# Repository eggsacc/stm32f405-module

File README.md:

<div align="center">

# STM32F405 Dev Module + BLDC hat

### MCU Dev
STM32F405RGT6 MCU dev module with commonly used peripherals broken out for easy access, and a dedicated CAN transceiver. Also includes 2 user programmable buttons and mini OLED display.

### BLDC Dev
BLDC hat based on the DRV8316C integrated driver. 6-PWM mode, 5-35V input, 5A continuous and 3-phase low-side current sensing. Suitable for FOC algorithm developement and testing for low current gimbal motors.

</div>

---

## MCU Pinout

<div align="center">

</div>

---

| Breakout / feature | Peripheral | Pin mapping |
|---|---|---|
| **UART header** | `USART3` | TX &rarr; `PC10`<br>RX &rarr; `PC11` |
| **SPI header** | `SPI1` | CS &rarr; `PA4`<br>SCK &rarr; `PA5`<br>MISO &rarr; `PA6`<br>MOSI &rarr; `PA7` |
| **I2C header** | `I2C1` | SCL &rarr; `PB6`<br>SDA &rarr; `PB7` |
| **CAN screw terminal** | `CAN1` (SN65HVD230) | TX &rarr; `PB9`<br>RX &rarr; `PB8` |
| **USB-C** | `USB_OTG_FS` | D&minus; &rarr; `PA11`<br>D+ &rarr; `PA12` |
| **SWD header** | `SYS` | SWDIO &rarr; `PA13`<br>SWCLK &rarr; `PA14` |
| **3-phase PWM header** | `TIM1` | <table><tbody><tr><td align="right">CH1 &rarr;</td><td><code>PA8</code></td><td align="right">&emsp;C1N &rarr;</td><td><code>PB13</code></td></tr><tr><td align="right">CH2 &rarr;</td><td><code>PA9</code></td><td align="right">&emsp;C2N &rarr;</td><td><code>PB0</code></td></tr><tr><td align="right">CH3 &rarr;</td><td><code>PA10</code></td><td align="right">&emsp;C3N &rarr;</td><td><code>PB1</code></td></tr></tbody></table> |
| **OLED** (on-board) | `I2C2` | SCL &rarr; `PB10`<br>SDA &rarr; `PB11` |
| **Utility buttons** (on-board) | `GPIO` / `EXTI` | L button &rarr; `PA2`<br>R button &rarr; `PA3` |
| **Crystal** (25MHz) | `RCC` HSE | OSC_IN &rarr; `PH0`<br>OSC_OUT &rarr; `PH1` |
| **GPIO header** (2&times;10) | free GPIO | <table><tbody><tr><td align="right">1 &rarr;</td><td><code>3.3V</code></td><td align="right">&emsp;2 &rarr;</td><td><code>3.3V</code></td></tr><tr><td align="right">3 &rarr;</td><td><code>5V</code></td><td align="right">&emsp;4 &rarr;</td><td><code>5V</code></td></tr><tr><td align="right">5 &rarr;</td><td><code>GND</code></td><td align="right">&emsp;6 &rarr;</td><td><code>GND</code></td></tr><tr><td align="right">7 &rarr;</td><td><code>PB4</code></td><td align="right">&emsp;8 &rarr;</td><td><code>PB3</code></td></tr><tr><td align="right">9 &rarr;</td><td><code>PC12</code></td><td align="right">&emsp;10 &rarr;</td><td><code>PC2</code></td></tr><tr><td align="right">11 &rarr;</td><td><code>PC3</code></td><td align="right">&emsp;12 &rarr;</td><td><code>PA0</code></td></tr><tr><td align="right">13 &rarr;</td><td><code>PA1</code></td><td align="right">&emsp;14 &rarr;</td><td><code>PC9</code></td></tr><tr><td align="right">15 &rarr;</td><td><code>PC8</code></td><td align="right">&emsp;16 &rarr;</td><td><code>PC7</code></td></tr><tr><td align="right">17 &rarr;</td><td><code>PC6</code></td><td align="right">&emsp;18 &rarr;</td><td><code>PB15</code></td></tr><tr><td align="right">19 &rarr;</td><td><code>PB14</code></td><td align="right">&emsp;20 &rarr;</td><td><code>PB12</code></td></tr></tbody></table> |

> Buttons are active-low to GND (3V3 pull-up).

---

## Power

>[!warning]Shared +5V rail
>5V rails are shared; do not connect USB and external power simultaneously!

- **USB-C**, 2-pin **`5V IN`** header, or `5V` on 2x10 breakout.
- AP2112K-3.3 LDO provides the 3.3 V rail (600 mA max).

---

## BLDC Hat hardware
<div align="center">

</div>

---
<div align="center">
Designed by <b>@eggsacc</b> · F405 Dev. V1.1<br>
Updated 22/09/2026
</div>

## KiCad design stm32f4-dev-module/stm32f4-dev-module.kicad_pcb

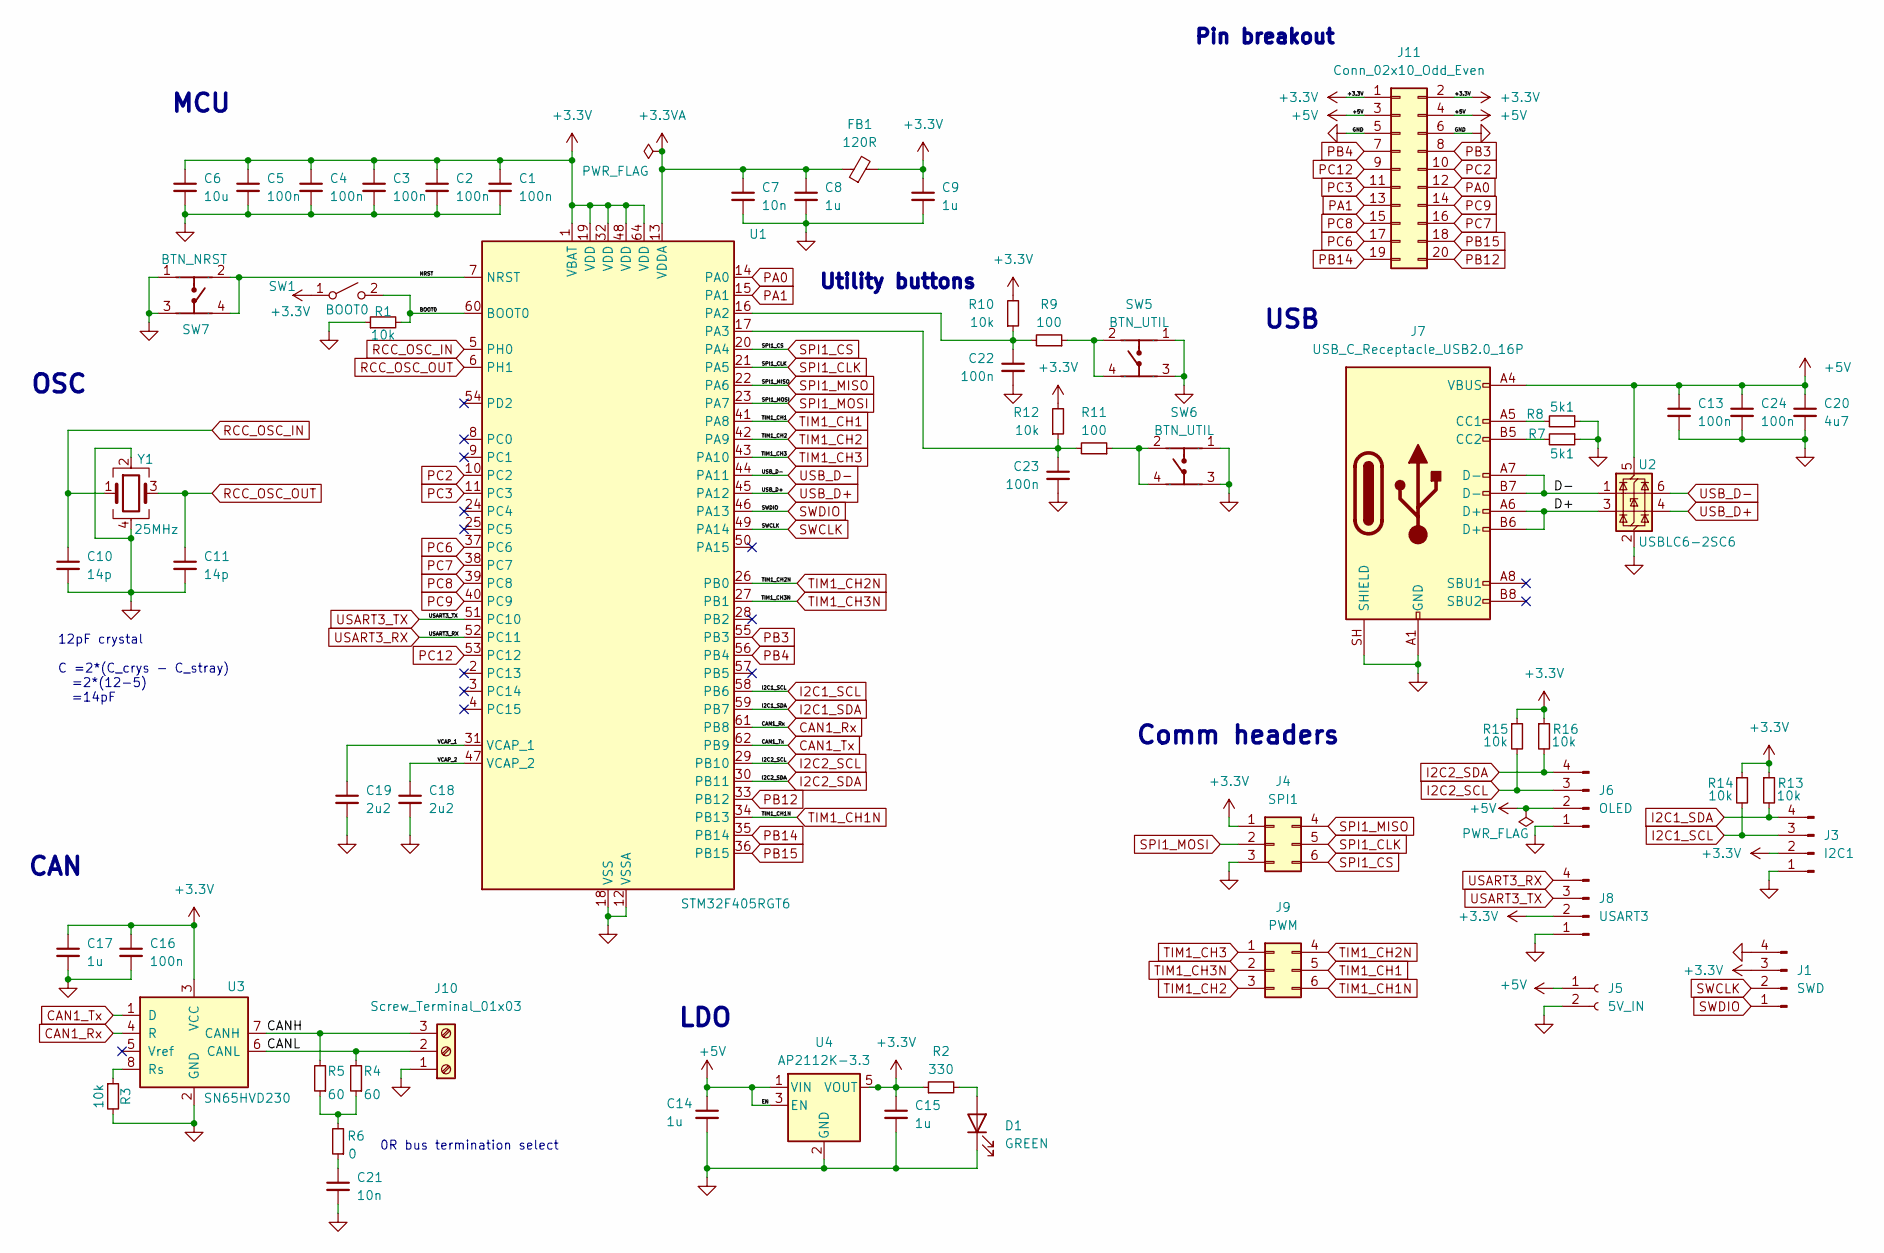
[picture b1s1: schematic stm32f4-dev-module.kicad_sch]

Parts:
C1, C2, C3, C4, C5, C13, C16, C22, C23, C24: 100n; C_0402_1005Metric
C6: 10u; C_0603_1608Metric
C7, C21: 10n; C_0402_1005Metric
C8, C9, C17: 1u; C_0402_1005Metric
C10, C11: 14p; C_0402_1005Metric
C14, C15: 1u; C_0603_1608Metric
C18, C19: 2u2; C_0603_1608Metric
C20: 4u7; C_0603_1608Metric
D1: GREEN; LED_0402_1005Metric
FB1: 120R; L_0603_1608Metric
J1: SWD; JST_SH_SM04B-SRSS-TB_1x04-1MP_P1.00mm_Horizontal
J3: I2C1; PinHeader_1x04_P2.54mm_Vertical
J4: SPI1; PinHeader_2x03_P2.54mm_Vertical
J5: 5V_IN; PinHeader_1x02_P2.54mm_Vertical
J6: OLED; OLED header
J7: USB_C_Receptacle_USB2.0_16P; USB_C_Receptacle_G-Switch_GT-USB-7010ASV
J8: USART3; PinHeader_1x04_P2.54mm_Vertical
J9: PWM; PinHeader_2x03_P2.54mm_Vertical
J10: Screw_Terminal_01x03; TerminalBlock_Phoenix_MKDS-1-3-3.81_1x03_P3.81mm_Horizontal
J11: Conn_02x10_Odd_Even; PinHeader_2x10_P2.54mm_Vertical
R1, R3, R10, R12, R13, R14, R15, R16: 10k; R_0402_1005Metric
R2: 330; R_0402_1005Metric
R4, R5: 60; R_0402_1005Metric
R6: 0; R_0603_1608Metric
R7, R8: 5k1; R_0402_1005Metric
R9, R11: 100; R_0402_1005Metric
SW1: BOOT0; SW_DIP_SPSTx01_Slide_6.7x4.1mm_W6.73mm_P2.54mm_LowProfile_J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
SW5, SW6: BTN_UTIL; SW-SMD_4P-L4.2-W3.4-P2.15-LS5.2; Manufacturer Part HX 3x4x2.5-PA-4N push button switch
SW7: BTN_NRST; SW-SMD_4P-L4.2-W3.4-P2.15-LS5.2; Manufacturer Part HX 3x4x2.5-PA-4N push button switch
U1: STM32F405RGT6; LQFP-64_10x10mm_P0.5mm
U2: USBLC6-2SC6; SOT-23-6
U3: SN65HVD230; SOIC-8_3.9x4.9mm_P1.27mm
U4: AP2112K-3.3; SOT-23-5_HandSoldering
Y1: 25MHz; Crystal_SMD_3225-4Pin_3.2x2.5mm

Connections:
+3.3V: C1.1, C2.1, C3.1, C4.1, C5.1, C6.1, C9.1, C15.1, C16.1, C17.1, FB1.2, J1.3, J3.2, J4.1, J8.2, J11.1, J11.2, R2.1, R10.2, R12.2, R13.1, R14.1, R15.1, R16.1, SW1.1 (A), U1.1 (VBAT), U1.19 (VDD), U1.32 (VDD), U1.48 (VDD), U1.64 (VDD), U3.3 (VCC), U4.5 (VOUT)
+3.3VA: C7.1, C8.1, FB1.1, U1.13 (VDDA)
+5V: C13.1, C14.1, C20.1, C24.1, J5.1, J6.2, J7.A4 (VBUS), J7.A9 (VBUS), J7.B4 (VBUS), J7.B9 (VBUS), J11.3, J11.4, U2.5 (VBUS), U4.1 (VIN), U4.3 (EN)
/BOOT0: R1.2, SW1.2 (B), U1.60 (BOOT0)
/CANH: J10.3, R5.2, U3.7 (CANH)
/CANL: J10.2, R4.2, U3.6 (CANL)
/D+: J7.A6 (D+), J7.B6 (D+), U2.3 (I/O2)
/D-: J7.A7 (D-), J7.B7 (D-), U2.1 (I/O1)
/NRST: SW7.2, SW7.4, U1.7 (NRST)
/VCAP_1: C19.1, U1.31 (VCAP_1)
/VCAP_2: C18.1, U1.47 (VCAP_2)
CAN1_Rx: U1.61 (PB8), U3.4 (R)
CAN1_Tx: U1.62 (PB9), U3.1 (D)
GND: C1.2, C2.2, C3.2, C4.2, C5.2, C6.2, C7.2, C8.2, C9.2, C10.2, C11.2, C13.2, C14.2, C15.2, C16.2, C17.2, C18.2, C19.2, C20.2, C21.2, C22.2, C23.2, C24.2, D1.1 (K), J1.4, J3.1, J4.3, J5.2, J6.1, J7.A1 (GND), J7.A12 (GND), J7.B1 (GND), J7.B12 (GND), J7.SH (SHIELD), J8.1, J10.1, J11.5, J11.6, R1.1, R3.2, R7.1, R8.1, SW5.1, SW5.3, SW6.1, SW6.3, SW7.1, SW7.3, U1.12 (VSSA), U1.18 (VSS), U1.63 (VSS), U2.2 (GND), U3.2 (GND), U4.2 (GND), Y1.2, Y1.4
I2C1_SCL: J3.3, R14.2, U1.58 (PB6)
I2C1_SDA: J3.4, R13.2, U1.59 (PB7)
I2C2_SCL: J6.3, R15.2, U1.29 (PB10)
I2C2_SDA: J6.4, R16.2, U1.30 (PB11)
unnamed: C21.1, R6.1
unnamed: D1.2 (A), R2.2
unnamed: J7.A5 (CC1), R8.2
unnamed: J7.B5 (CC2), R7.2
unnamed: R4.1, R5.1, R6.2
unnamed: R9.1, SW5.2, SW5.4
unnamed: R11.1, SW6.2, SW6.4
unnamed: C22.1, R9.2, R10.1, U1.16 (PA2)
unnamed: C23.1, R11.2, R12.1, U1.17 (PA3)
unnamed: R3.1, U3.8 (Rs)
PA0: J11.12, U1.14 (PA0)
PA1: J11.13, U1.15 (PA1)
PB3: J11.8, U1.55 (PB3)
PB4: J11.7, U1.56 (PB4)
PB12: J11.20, U1.33 (PB12)
PB14: J11.19, U1.35 (PB14)
PB15: J11.18, U1.36 (PB15)
PC2: J11.10, U1.10 (PC2)
PC3: J11.11, U1.11 (PC3)
PC6: J11.17, U1.37 (PC6)
PC7: J11.16, U1.38 (PC7)
PC8: J11.15, U1.39 (PC8)
PC9: J11.14, U1.40 (PC9)
PC12: J11.9, U1.53 (PC12)
RCC_OSC_IN: C10.1, U1.5 (PH0), Y1.1
RCC_OSC_OUT: C11.1, U1.6 (PH1), Y1.3
SPI1_CLK: J4.5, U1.21 (PA5)
SPI1_CS: J4.6, U1.20 (PA4)
SPI1_MISO: J4.4, U1.22 (PA6)
SPI1_MOSI: J4.2, U1.23 (PA7)
SWCLK: J1.2, U1.49 (PA14)
SWDIO: J1.1, U1.46 (PA13)
TIM1_CH1: J9.5, U1.41 (PA8)
TIM1_CH1N: J9.6, U1.34 (PB13)
TIM1_CH2: J9.3, U1.42 (PA9)
TIM1_CH2N: J9.4, U1.26 (PB0)
TIM1_CH3: J9.1, U1.43 (PA10)
TIM1_CH3N: J9.2, U1.27 (PB1)
USART3_RX: J8.4, U1.52 (PC11)
USART3_TX: J8.3, U1.51 (PC10)
USB_D+: U1.45 (PA12), U2.4 (I/O2)
USB_D-: U1.44 (PA11), U2.6 (I/O1)

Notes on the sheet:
MCU
Pin breakout
Comm headers
CAN
12pF crystal C =2*(C_crys - C_stray) =2*(12-5) =14pF
USB
Utility buttons
LDO
OSC
0R bus termination select

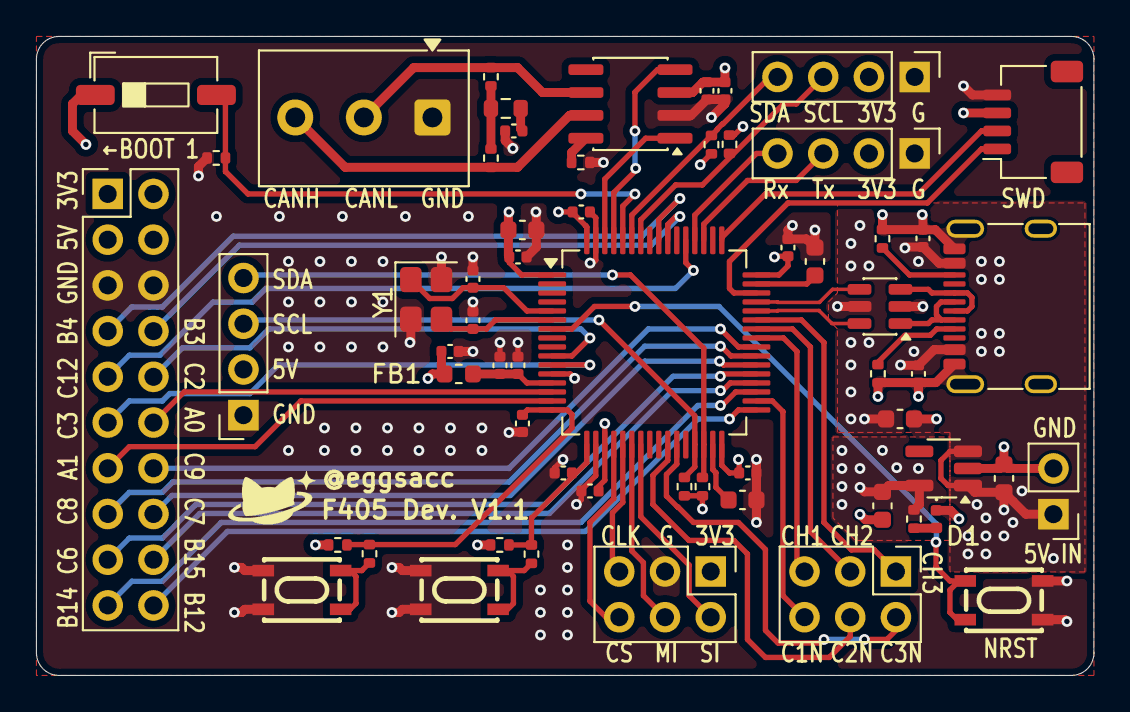
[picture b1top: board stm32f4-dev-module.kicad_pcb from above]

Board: 4 copper layers, 58.8 x 35.5 mm, 60 parts (0 on the bottom side), 60 nets.

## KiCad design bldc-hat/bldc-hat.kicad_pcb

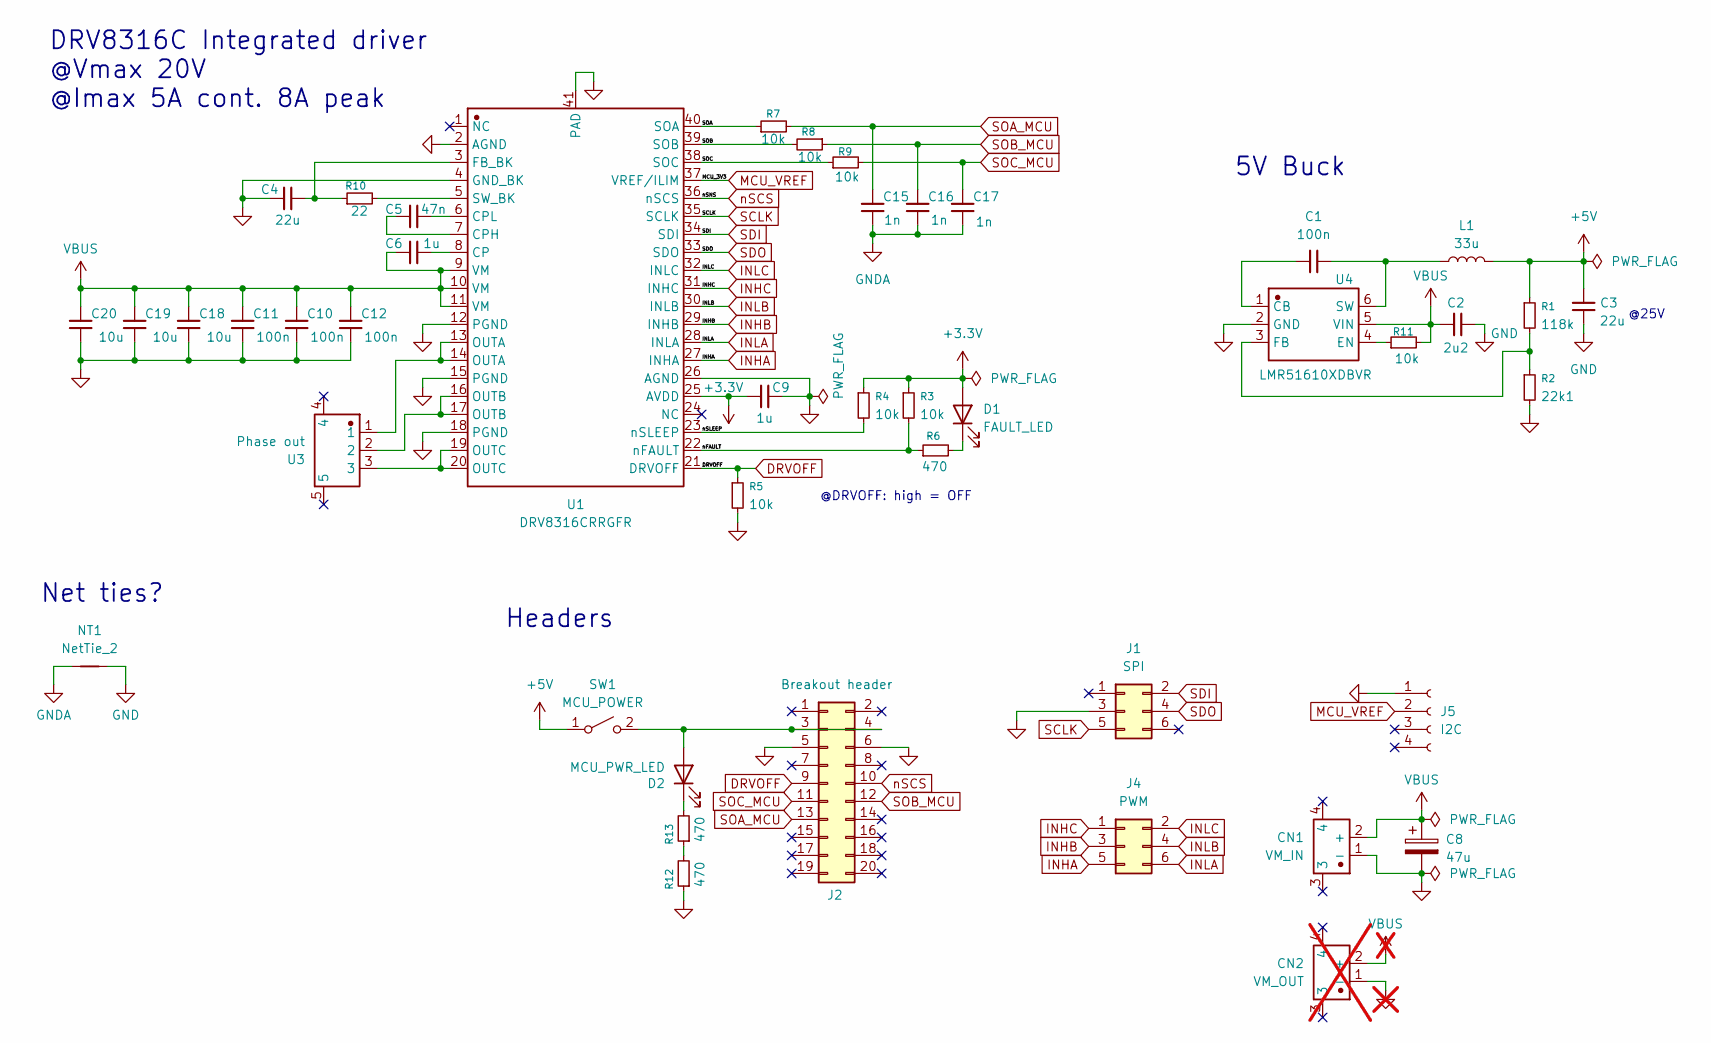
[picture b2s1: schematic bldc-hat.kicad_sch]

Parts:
C1, C10, C11, C12: 100n; C_0402_1005Metric
C2: 2u2; C_1206_3216Metric
C3: 22u; C_1210_3225Metric
C4: 22u; C_0805_2012Metric
C5: 47n; C_0603_1608Metric
C6: 1u; C_0603_1608Metric
C8: 47u; CP_Elec_6.3x7.7
C9: 1u; C_0402_1005Metric
C15, C16, C17: 1n; C_0402_1005Metric
C18, C19, C20: 10u; C_1210_3225Metric
CN1: VM_IN; CONN-TH_XT30PW-M; Manufacturer Part XT30PW-M
CN2: VM_OUT; CONN-TH_XT30PW-M; Manufacturer Part XT30PW-M; not fitted
D1: FAULT_LED; LED_0402_1005Metric
D2: MCU_PWR_LED; LED_0402_1005Metric
J1: SPI; PinHeader_2x03_P2.54mm_Vertical
J2: Breakout header; PinHeader_2x10_P2.54mm_Vertical
J4: PWM; PinHeader_2x03_P2.54mm_Vertical
J5: I2C; PinHeader_1x04_P2.54mm_Vertical
L1: 33u; L_6.3x6.3_H3
NT1: NetTie_2; NetTie-2_SMD_Pad0.5mm
R1: 118k; R_0402_1005Metric
R2: 22k1; R_0402_1005Metric
R3, R4, R5, R7, R8, R9, R11: 10k; R_0402_1005Metric
R6, R12, R13: 470; R_0402_1005Metric
R10: 22; R_0402_1005Metric
SW1: MCU_POWER; SW_DIP_SPSTx01_Slide_6.7x4.1mm_W6.73mm_P2.54mm_LowProfile_J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
U1: DRV8316CRRGFR; DRV8316CR; Manufacturer Part DRV8316CRRGFR
U3: Phase out; CONN-TH_MR30PW-M30-G-Y; Manufacturer Part MR30PW-M30.G.Y
U4: LMR51610XDBVR; SOT-23-6; Manufacturer Part LMR51610XDBVR

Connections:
+3.3V: C9.1, D1.2 (A), R3.1, R4.1, U1.25 (AVDD)
+5V: C3.1, L1.2, R1.1, SW1.1 (A)
/SOA: R7.1, U1.40 (SOA)
/SOB: R8.2, U1.39 (SOB)
/SOC: R9.1, U1.38 (SOC)
/nFAULT: R3.2, R6.1, U1.22 (nFAULT)
/nSLEEP: R4.2, U1.23 (nSLEEP)
DRVOFF: J2.9, R5.1, U1.21 (DRVOFF)
GND: C2.1, C3.2, C4.2, C8.2, C9.2, C10.2, C11.2, C12.2, C18.2, C19.2, C20.2, CN1.1 (-), CN2.1 (-), J1.3, J2.5, J2.6, J5.1, NT1.2, R2.2, R5.2, R12.1, U1.2 (AGND), U1.4 (GND_BK), U1.12 (PGND), U1.15 (PGND), U1.18 (PGND), U1.26 (AGND), U1.41 (PAD), U4.2 (GND); also elsewhere on the board
GNDA: C15.2, C16.2, C17.2, NT1.1; also elsewhere on the board
INHA: J4.5, U1.27 (INHA)
INHB: J4.3, U1.29 (INHB)
INHC: J4.1, U1.31 (INHC)
INLA: J4.6, U1.28 (INLA)
INLB: J4.4, U1.30 (INLB)
INLC: J4.2, U1.32 (INLC)
MCU_VREF: J5.2, U1.37 (VREF/ILIM)
unnamed: D1.1 (K), R6.2
unnamed: D2.2 (A), J2.3, J2.4, SW1.2 (B)
unnamed: D2.1 (K), R13.2
unnamed: R12.2, R13.1
unnamed: C6.2, U1.8 (CP)
unnamed: C5.1, U1.7 (CPH)
unnamed: C5.2, U1.6 (CPL)
unnamed: C4.1, R10.1, U1.3 (FB_BK)
unnamed: U1.13 (OUTA), U1.14 (OUTA), U3.1
unnamed: U1.16 (OUTB), U1.17 (OUTB), U3.2
unnamed: U1.19 (OUTC), U1.20 (OUTC), U3.3
unnamed: R10.2, U1.5 (SW_BK)
unnamed: C1.1, U4.1 (CB)
unnamed: R11.1, U4.4 (EN)
unnamed: R1.2, R2.1, U4.3 (FB)
unnamed: C1.2, L1.1, U4.6 (SW)
SCLK: J1.5, U1.35 (SCLK)
SDI: J1.2, U1.34 (SDI)
SDO: J1.4, U1.33 (SDO)
SOA_MCU: C15.1, J2.13, R7.2
SOB_MCU: C16.1, J2.12, R8.1
SOC_MCU: C17.1, J2.11, R9.2
VBUS: C2.2, C6.1, C8.1, C10.1, C11.1, C12.1, C18.1, C19.1, C20.1, CN1.2 (+), CN2.2 (+), R11.2, U1.9 (VM), U1.10 (VM), U1.11 (VM), U4.5 (VIN)
nSCS: J2.10, U1.36 (nSCS)

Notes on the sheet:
DRV8316C Integrated driver @Vmax 20V @Imax 5A cont. 8A peak
@DRVOFF: high = OFF
Net ties?
5V Buck
Headers
@25V

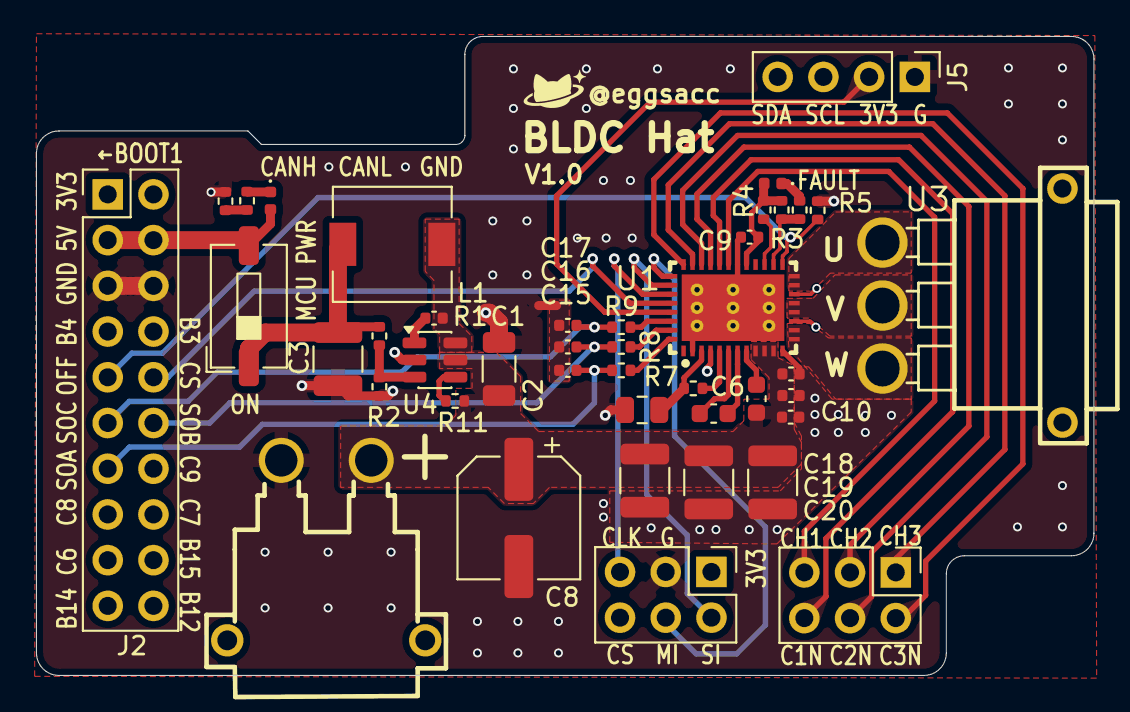
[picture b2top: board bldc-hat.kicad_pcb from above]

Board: 4 copper layers, 58.8 x 35.5 mm, 43 parts (0 on the bottom side), 41 nets.

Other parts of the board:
NT3: NetTie_2; NetTie-2_SMD_Pad0.5mm

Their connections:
GND: NT3.2; also elsewhere on the board
GNDA: NT3.1; also elsewhere on the board

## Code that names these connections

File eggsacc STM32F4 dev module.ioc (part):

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Mcu.Name=STM32F405RGTx
Mcu.Package=LQFP64
Mcu.UserName=STM32F405RGTx
PA0-WKUP.Signal=ADCx_IN0
PA1.Signal=ADCx_IN1
PA10.Signal=S_TIM1_CH3
PA11.Mode=Device_Only
PA11.Signal=USB_OTG_FS_DM
PA12.Mode=Device_Only
PA12.Signal=USB_OTG_FS_DP
PA13.Mode=Serial_Wire
PA13.Signal=SYS_JTMS-SWDIO
PA14.Mode=Serial_Wire
PA14.Signal=SYS_JTCK-SWCLK
PA2.GPIOParameters=GPIO_Label
PA2.GPIO_Label=GPIO_EXTI2(Push1)
PA2.Signal=GPXTI2
PA3.GPIOParameters=GPIO_Label
PA3.GPIO_Label=GPIO_EXTI3(Push2)
PA3.Signal=GPXTI3
PA4.GPIOParameters=GPIO_Label
PA4.GPIO_Label=SPI1_CS
PA4.Signal=GPIO_Output
PA5.Mode=Full_Duplex_Master
PA5.Signal=SPI1_SCK
PA6.Mode=Full_Duplex_Master
PA6.Signal=SPI1_MISO
PA7.Mode=Full_Duplex_Master
PA7.Signal=SPI1_MOSI
PA8.Signal=S_TIM1_CH1
PA9.Signal=S_TIM1_CH2
PB0.Mode=PWM Generation2 CH2 CH2N
PB0.Signal=TIM1_CH2N
PB1.Mode=PWM Generation3 CH3 CH3N
PB1.Signal=TIM1_CH3N
PB10.GPIOParameters=GPIO_Label
PB10.GPIO_Label=I2C2_SCL(OLED)
PB10.Mode=I2C
PB10.Signal=I2C2_SCL
PB11.GPIOParameters=GPIO_Label
PB11.GPIO_Label=I2C2_SDA(OLED)
PB11.Mode=I2C
PB11.Signal=I2C2_SDA
PB13.Mode=PWM Generation1 CH1 CH1N
PB13.Signal=TIM1_CH1N
PB6.Mode=I2C
PB6.Signal=I2C1_SCL
PB7.Mode=I2C
PB7.Signal=I2C1_SDA
PB8.Mode=CAN_Activate
PB8.Signal=CAN1_RX
PB9.Mode=CAN_Activate
PB9.Signal=CAN1_TX
PC10.Mode=Asynchronous
PC10.Signal=USART3_TX
PC11.Mode=Asynchronous
PC11.Signal=USART3_RX
PC3.Signal=ADCx_IN13
PH0-OSC_IN.Mode=HSE-External-Oscillator
PH0-OSC_IN.Signal=RCC_OSC_IN
PH1-OSC_OUT.Mode=HSE-External-Oscillator
PH1-OSC_OUT.Signal=RCC_OSC_OUT
RCC.HSE_VALUE=25000000
RCC.SYSCLKFreq_VALUE=168000000
RCC.SYSCLKSource=RCC_SYSCLKSOURCE_PLLCLK
board=custom

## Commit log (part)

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2026-06-10 commmit
